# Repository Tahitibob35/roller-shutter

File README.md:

# roller-shutter
Somfy roller shutter controlled by an ESP32

## Materials

### ESP32 from azdelivery

### RF433 module

### 433.42MHz oscillator

### Somfy RTS module

## First run or rescue mode

Keep pressed on the rescue button (pin 14) and press the ESP32 reset button.

The ESP32 start in rescue mode as an access point.

* Access point : "VoletRoulants"

* Default IP : 10.10.10.1

Configuration URL : http://roller/config

Set your wifi credentials in the wifi page and restart the ESP32.

* Home page URL : http://X.X.X.X

* Configuration page URL : http://X.X.X.X/config

## Attach a roller shutter

Press the "Prog" button 3 seconds

Go to the "Attacher" page and click on the desired roller shutter

## Screenshots

* Main page

* Configuration page

* Programs page

* Wifi page

* Clock page

* Schema

## Photos

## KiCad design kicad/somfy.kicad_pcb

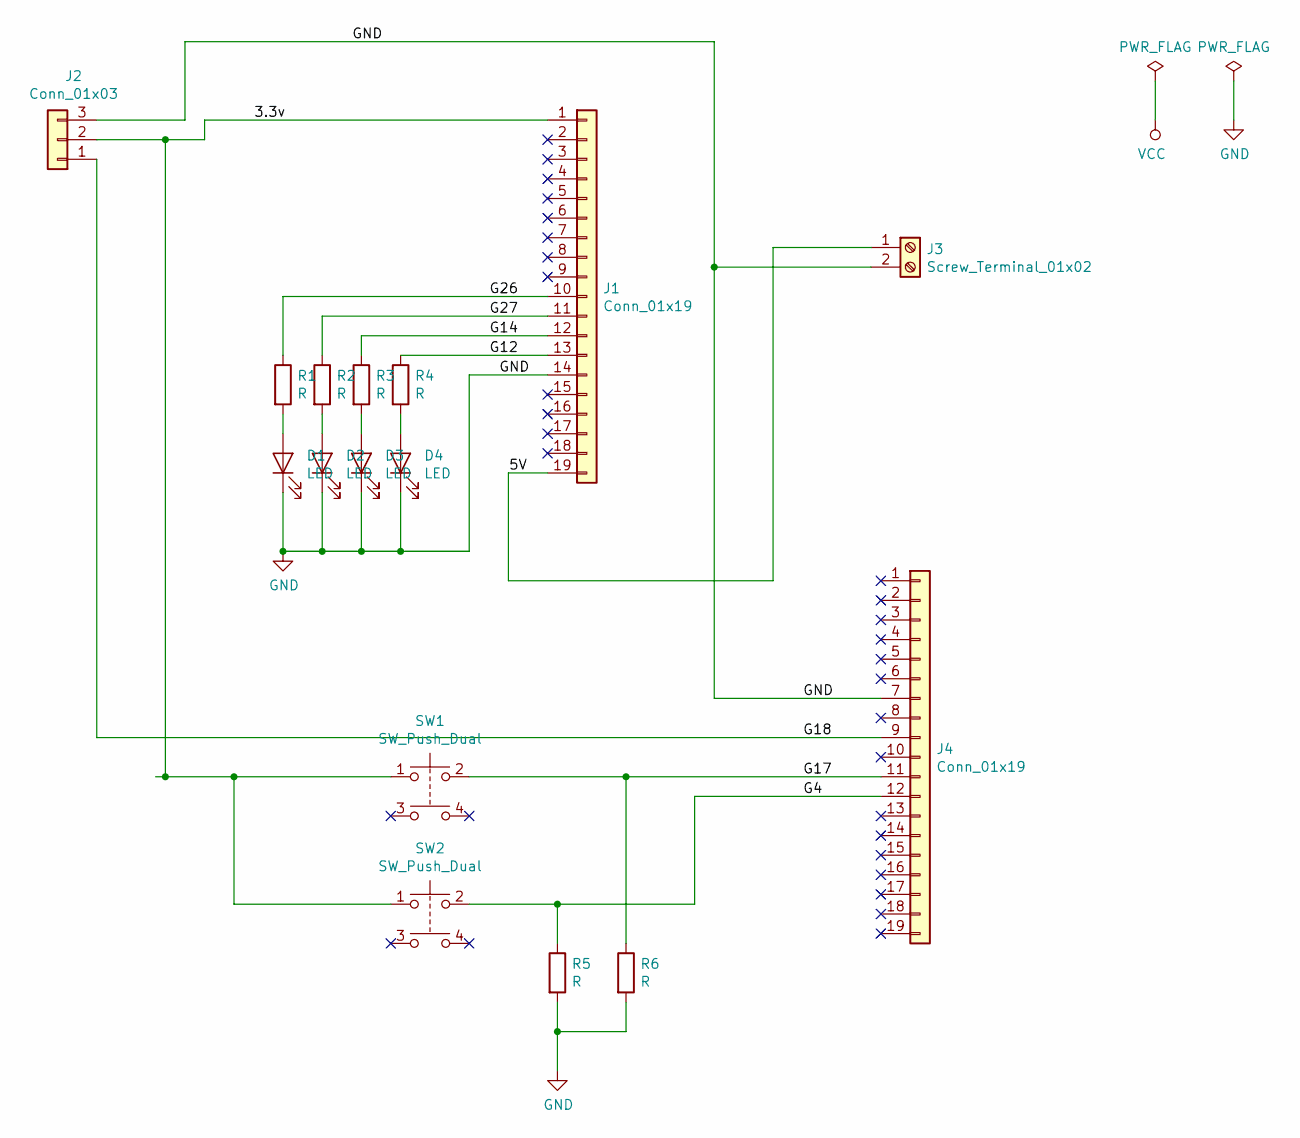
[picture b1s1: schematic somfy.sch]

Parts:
D1, D2, D3, D4: LED; LED_D3.0mm
J1, J4: Conn_01x19; PinHeader_1x19_P2.54mm_Vertical
J2: Conn_01x03; PinHeader_1x03_P2.54mm_Vertical
J3: Screw_Terminal_01x02; PinHeader_1x02_P2.54mm_Vertical
R1, R2, R3, R4, R5, R6: R; R_Axial_DIN0309_L9.0mm_D3.2mm_P15.24mm_Horizontal
SW1, SW2: SW_Push_Dual; SW_Tactile_Straight_KSA0Axx1LFTR

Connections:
/3.3v: J1.1, J2.2, SW1.1, SW2.1
/5V: J1.19, J3.1
/G4: J4.12, R5.1, SW2.2
/G12: J1.13, R4.1
/G14: J1.12, R3.1
/G17: J4.11, R6.1, SW1.2
/G18: J2.1, J4.9
/G26: J1.10, R1.1
/G27: J1.11, R2.1
GND: D1.1 (K), D2.1 (K), D3.1 (K), D4.1 (K), J1.14, J2.3, J3.2, J4.7, R5.2, R6.2
unnamed: D1.2 (A), R1.2
unnamed: D2.2 (A), R2.2
unnamed: D3.2 (A), R3.2
unnamed: D4.2 (A), R4.2

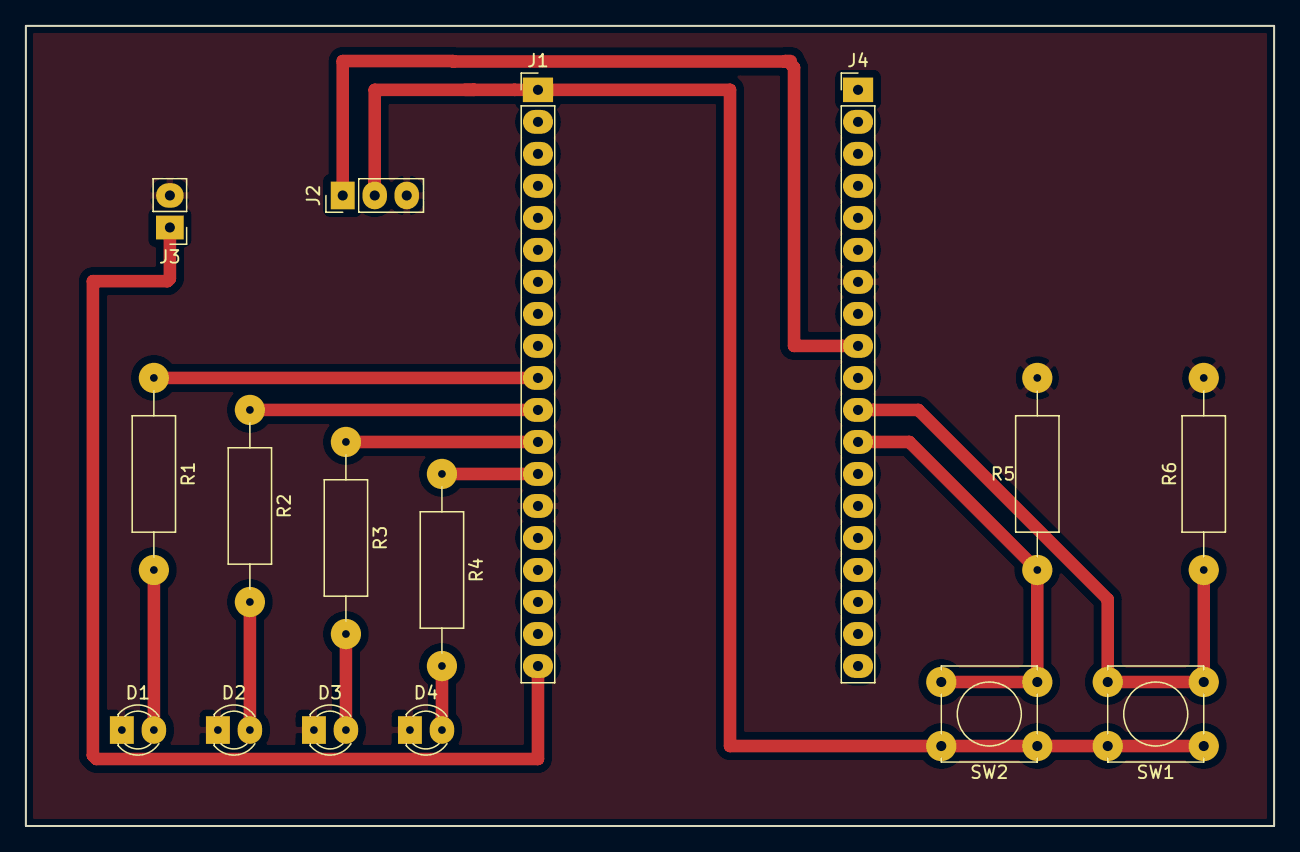
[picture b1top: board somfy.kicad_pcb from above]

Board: 2 copper layers, 99.1 x 63.5 mm, 16 parts (0 on the bottom side), 14 nets.

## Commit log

2020-06-28 Add Kicad PCB files
2020-06-28 Fix html rendering
2020-06-28 Add images
2020-06-28 Change pins
2020-07-05 Change CPU freq and pins
2020-07-05 Remove debug prgms
2020-07-05 Remove unused variables
2020-07-05 prgm trigger really sends commands
2020-07-05 Add somfy image
2020-07-05 Add photos
2020-07-14 Add3 seconds between 2 commands
2020-07-19 Add captive portal and enable debug log level
2020-07-19 Minor fix
2020-07-19 Add a manual command : stop
2020-07-20 misc changes
2020-08-09 Add check in prgm form
2020-09-06 Fix time setup on startup
2020-12-24 remote_name as variable
2020-12-28 Use Task Sheduler instead of high CPU load loop
2020-12-30 Fix compilation warning
2020-12-30 Feature: new api page (protected by token) Feature: write output to a syslog server Fix: ping default gateway for wifi health check
2021-01-07 Make programs working again
2021-01-07 remove vars.h from git
2021-01-08 Server NTP sauvé en prefs
2021-01-08 Olivier remote names
2021-01-08 Remove delay from Somfy move functions (replaced by a task)
2021-01-09 Update to ESPAsyncWebServer (instead of WebServer)
2021-01-10 test optional delay_after_move
2021-01-10 Fix typo
2021-05-09 Rolling code per remote
2021-05-09 Fix comments
2021-05-09 Status led HIGH when checking wifi
